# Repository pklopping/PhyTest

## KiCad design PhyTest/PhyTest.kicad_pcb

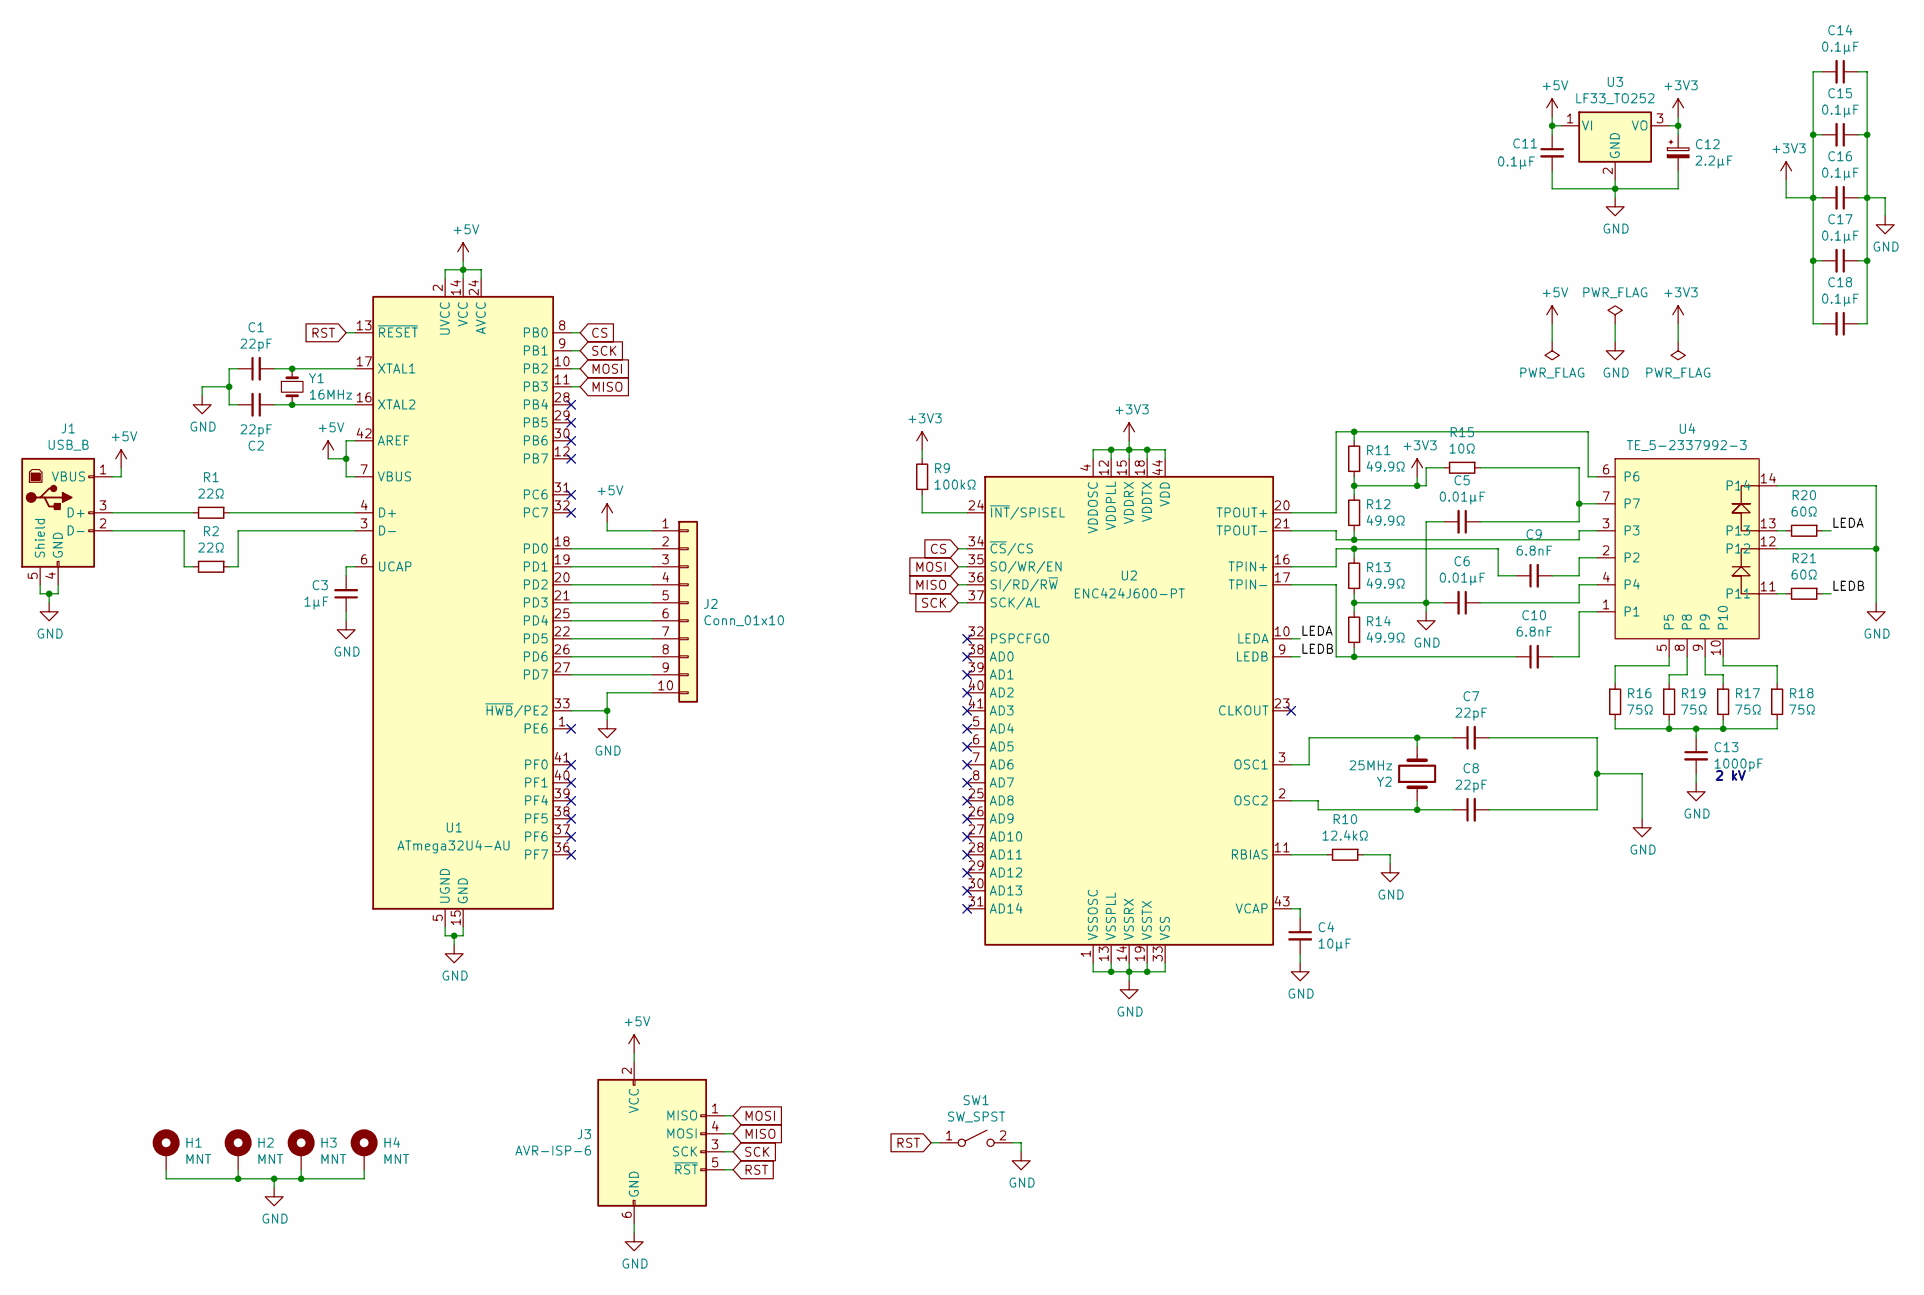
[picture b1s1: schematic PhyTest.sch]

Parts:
C1, C2, C7, C8: 22pF; C_0805_2012Metric
C3: 1µF; C_0805_2012Metric
C4: 10µF; C_0805_2012Metric
C5, C6: 0.01µF; C_0805_2012Metric
C9, C10: 6.8nF; C_0805_2012Metric
C11, C14, C15, C16, C17, C18: 0.1µF; C_0805_2012Metric
C12: 2.2µF; C_Elec_10x10.2
C13: 1000pF; R_1206_3216Metric; Voltage 2 kV
H1, H2, H3, H4: MNT; MountingHole_3.2mm_M3_Pad_Via
J1: USB_B; 1-1734346-1_1
J2: Conn_01x10; PinHeader_1x10_P2.54mm_Vertical
J3: AVR-ISP-6; PinHeader_2x03_P2.54mm_Vertical_SMD
R1, R2: 22Ω; R_0805_2012Metric
R9: 100kΩ; R_0805_2012Metric
R10: 12.4kΩ; R_0805_2012Metric
R11, R12, R13, R14: 49.9Ω; R_0805_2012Metric
R15: 10Ω; R_0805_2012Metric
R16, R17, R18, R19: 75Ω; R_0805_2012Metric
R20, R21: 60Ω; R_0805_2012Metric
SW1: SW_SPST; SKTHACE010
U1: ATmega32U4-AU; TQFP-44_10x10mm_P0.8mm
U2: ENC424J600-PT; TQFP-44_10x10mm_P0.8mm
U3: LF33_TO252; TO-252-2
U4: TE_5-2337992-3; TE-5-2337992-3
Y1: 16MHz; Crystal_SMD_HC49-SD
Y2: 25MHz; Crystal_SMD_HC49-SD

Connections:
+3V3: C12.1, C14.2, C15.2, C16.2, C17.2, C18.2, R9.2, R11.1, R12.2, R15.2, U2.4 (VDDOSC), U2.12 (VDDPLL), U2.15 (VDDRX), U2.18 (VDDTX), U2.44 (VDD), U3.3 (VO)
+5V: C11.1, J1.1 (VBUS), J2.1, J3.2 (VCC), U1.2 (UVCC), U1.7 (VBUS), U1.14 (VCC), U1.24 (AVCC), U1.34 (VCC), U1.42 (AREF), U1.44 (AVCC), U3.1 (VI); also elsewhere on the board
/LEDA: R20.1, U2.10 (LEDA)
/LEDB: R21.1, U2.9 (LEDB)
CS: U1.8 (PB0), U2.34 (~CS~/CS)
GND: C1.1, C2.2, C3.1, C4.2, C5.2, C6.2, C7.2, C8.2, C11.2, C12.2, C13.2, C14.1, C15.1, C16.1, C17.1, C18.1, H1.1, H2.1, H3.1, H4.1, J1.4 (GND), J1.5 (Shield), J2.10, J3.6 (GND), R10.1, R13.1, R14.2, SW1.2 (B), U1.5 (UGND), U1.15 (GND), U1.23 (GND), U1.33 (~HWB~/PE2), U1.35 (GND), U1.43 (GND), U2.1 (VSSOSC), U2.13 (VSSPLL), U2.14 (VSSRX), U2.19 (VSSTX), U2.22 (VSSTX), U2.33 (VSS), U2.42 (VSS), U3.2 (GND), U4.12, U4.14; also elsewhere on the board
MISO: J3.4 (MOSI), U1.11 (PB3), U2.36 (SI/RD/R~W)
MOSI: J3.1 (MISO), U1.10 (PB2), U2.35 (SO/WR/EN)
unnamed: C1.2, U1.17 (XTAL1), Y1.1
unnamed: C2.1, U1.16 (XTAL2), Y1.2
unnamed: C3.2, U1.6 (UCAP)
unnamed: C4.1, U2.43 (VCAP)
unnamed: C5.1, R15.1, U4.7
unnamed: C6.1, U4.4
unnamed: C7.1, U2.3 (OSC1), Y2.2
unnamed: C8.1, U2.2 (OSC2), Y2.1
unnamed: C9.1, R13.2, U2.16 (TPIN+)
unnamed: C9.2, U4.2
unnamed: C10.1, R14.1, U2.17 (TPIN-)
unnamed: C10.2, U4.1
unnamed: C13.1, R16.2, R17.2, R18.2, R19.2
unnamed 21: J1.2 (D-), R2.2; also elsewhere on the board
unnamed 22: J1.3 (D+), R1.2; also elsewhere on the board
unnamed: J2.2, U1.18 (PD0)
unnamed: J2.3, U1.19 (PD1)
unnamed: J2.4, U1.20 (PD2)
unnamed: J2.5, U1.21 (PD3)
unnamed: J2.6, U1.25 (PD4)
unnamed: J2.7, U1.22 (PD5)
unnamed: J2.8, U1.26 (PD6)
unnamed: J2.9, U1.27 (PD7)
unnamed: R1.1, U1.4 (D+)
unnamed: R2.1, U1.3 (D-)
unnamed: R9.1, U2.24 (~INT~/SPISEL)
unnamed: R10.2, U2.11 (RBIAS)
unnamed: R11.2, U2.20 (TPOUT+), U4.6
unnamed: R12.1, U2.21 (TPOUT-), U4.3
unnamed: R16.1, U4.5
unnamed: R17.1, U4.9
unnamed: R18.1, U4.10
unnamed: R19.1, U4.8
unnamed: R20.2, U4.13
unnamed: R21.2, U4.11
RST: J3.5 (~RST), SW1.1 (A), U1.13 (~RESET)
SCK: J3.3 (SCK), U1.9 (PB1), U2.37 (SCK/AL)

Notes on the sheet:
2 kV

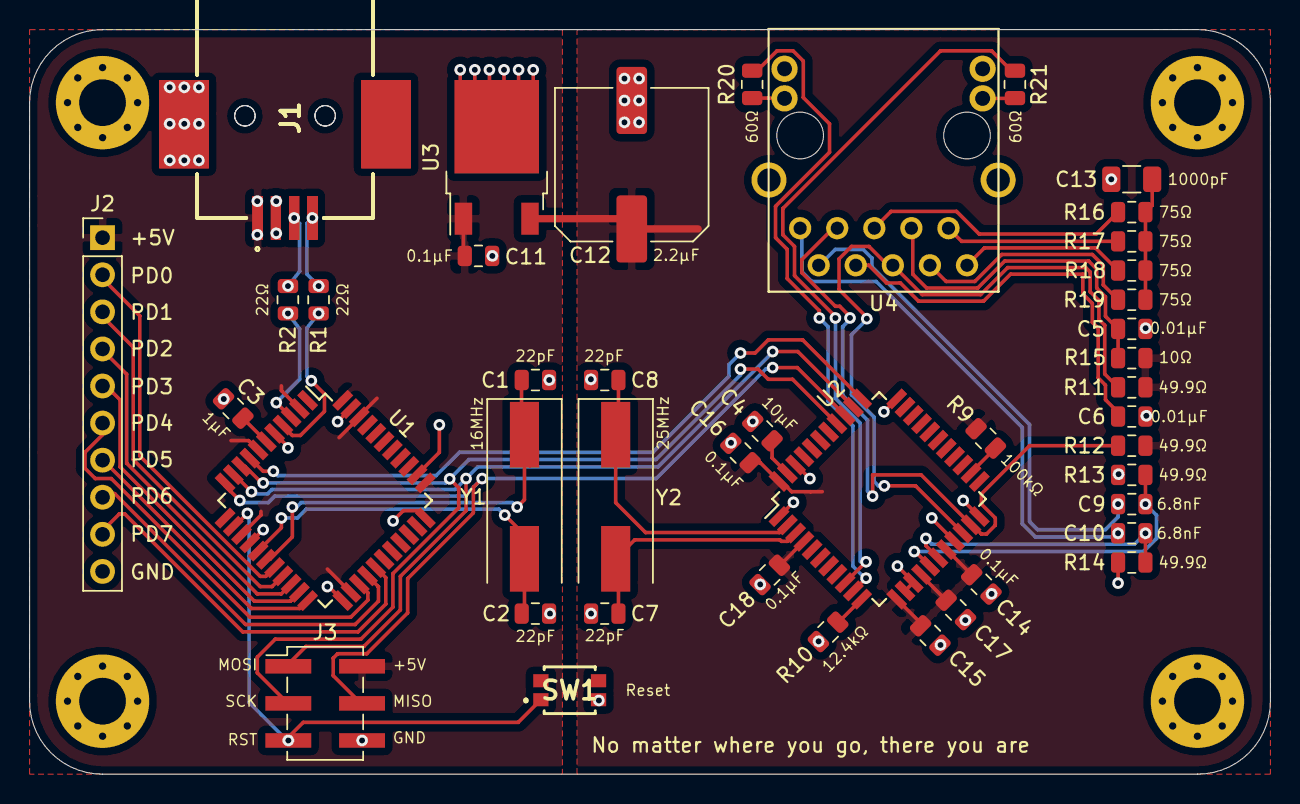
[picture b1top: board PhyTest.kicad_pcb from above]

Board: 2 copper layers, 85.0 x 51.0 mm, 48 parts (0 on the bottom side), 45 nets.

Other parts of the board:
J1#2: USB_B; 1-1734346-1_1

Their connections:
+5V: J1#2.1; also elsewhere on the board
GND: J1#2.4, J1#2.5; also elsewhere on the board
unnamed 21: J1#2.2; also elsewhere on the board
unnamed 22: J1#2.3; also elsewhere on the board

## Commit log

2021-06-22 Adding a microcontroller, kinda
2021-07-06 Added LEDs, started picking components
2021-07-06 Picking out more components
2021-07-07 The USB footprint looks... wrong
2021-07-07 Starting layout
2021-07-07 More layout
2021-07-08 Layout complete?
2021-07-08 Updating datasheets
2021-07-09 Adding RJ45 model, separating clocks
2021-07-09 Updating RJ45 footprint
2021-07-10 Finalizing layout
2021-07-12 Updating library paths to be relative so it'll work on more than one computer
2021-07-26 Workign on reset button and ICSP headers
2021-07-27 Rev A
2021-07-27 Updating silkscreen rev number
